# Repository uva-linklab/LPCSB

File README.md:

# LPCSB
LPCSB = Low Power Color Sensing Board

The LPCSB is designed to measure the ambient light in the surrounding area by means of a TCS34725 Color Sensor.  The sensor uses four analog-to-digital converters (ADCs) to read four photodiodes (one photodiode per ADC).  The photodiodes are red-filtered, green-filtered, blue-filtered, and clear (no filter).  The photodiodes are also covered with an IR-blocking filter.  The code in the "software" folder of this repository is responsible for initializing all of the hardware on the LPCSB, configuring the settings of the color sensor (integration time, gain, enabling the internal oscillator, enabling the ADCs, and setting a hardware interrupt in the sensor), reading and saving the values taken by the four ADCs mentioned previously, and then calculating the the temperature of each color (how much of each is in the sample taken), as well as the lux (intensity per square meter) of said sample.  The measured color temperatures along with the calculated values are broadcast through the BLE radio built into the nrf51822 processor used in this board several times, with new measurements being taken every five seconds.  

There is also a data-processing algorithm that is meant to operate on a desktop computer, using  a Bluetooth receiver - see thesis for the specific one - to capture the transmitted data from the LPCSB and save it to an Excel spreadsheet.  Depending on the version of the algorithm being used, it can also classify the type of light measured by the LPCSB before saving the data to Excel.  When running tests with the LPCSB, make sure that the algorithm is running BEFORE activating the LPCSB to avoid errors with the algorithm in its current state.

SIDE NOTE:  Make sure that the external crystal oscillator meets the BLE chip requirements for the external clock frequency described in the nrf51822 datasheet. In this case, the required frequency for the external clock is 16 MHz.  For some reason, the clock chips that were being used early on were 26 MHz clocks instead of 16 MHz, which WILL cause errors with whichever sections of the processor happen to rely on the external signal (in this case, the BLE Radio parts).

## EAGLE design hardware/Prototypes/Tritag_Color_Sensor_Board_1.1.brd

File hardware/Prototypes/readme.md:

# Version 1:

The files in this folder hold prototype schematics for potential additions for the LPCSB (layout and schematic files).

Label the prototype files as follows: LPCSB_Color_[insert new sensor name here]_[board or schematic]

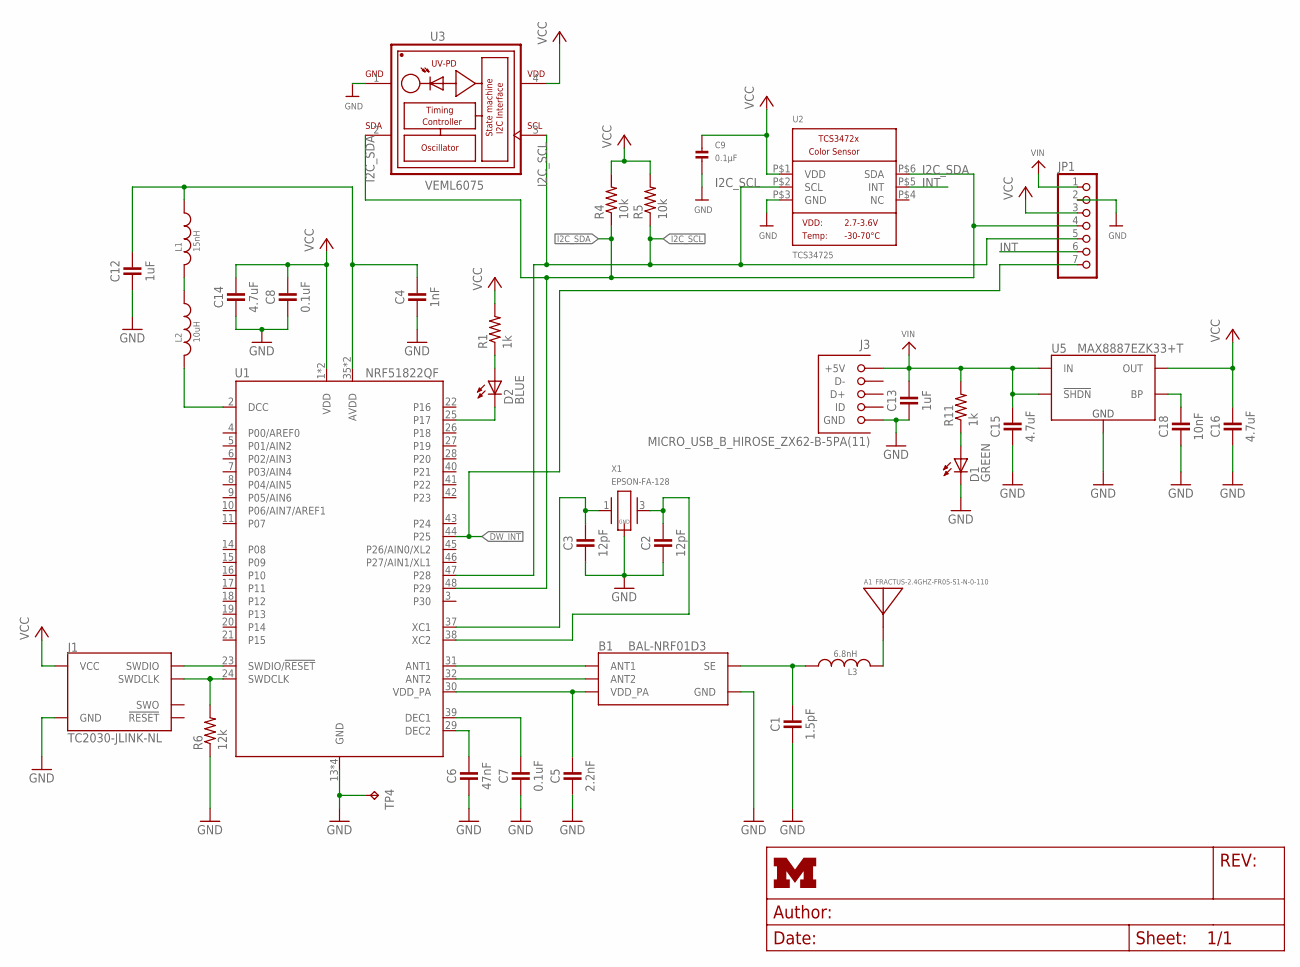
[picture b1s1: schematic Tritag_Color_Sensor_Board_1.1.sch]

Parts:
A1: FRACTUS-2.4GHZ-FR05-S1-N-0-110; FRACTUS-ANTENNA-FR05-S1-N-0-110
B1: BAL-NRF01D3
C1: 1.5pF; 0402_CAP
C2, C3: 12pF; 0402_CAP
C4: 1nF; 0402_CAP
C5: 2.2nF; 0402_CAP
C6: 47nF; 0402_CAP
C7, C8: 0.1uF; 0402_CAP
C9: 0.1µF; _0805
C12, C13: 1uF; 0402_CAP
C14, C15, C16: 4.7uF; 0402_CAP
C18: 10nF; 0402_CAP
D1: GREEN; LED-0603
D2: BLUE; LED-0603
J1: TC2030-JLINK-NL; TC2030-IDC-NL
J3: MICRO_USB_B_HIROSE_ZX62-B-5PA(11); USB_MICRO_B-HIROSE-ZX62-B-5PA(11)
JP1: HEADER-1X770MIL; 1X07_ROUND_70
L1: 15nH; 0402_CAP
L2: 10uH; 0603_CAP
L3: 6.8nH; 0402_CAP
R1, R11: 1k; 0402_RES
R4, R5: 10k; 0402_RES
R6: 12k; 0402_RES
TP4: TPTP06SQ; TP06SQ
U1: NRF51822QF; QFN-48-6MM
U2: TCS34725; TCS3472_FN6
U3: VEML6075; VISHAY_VEML6075_1.25X2X1
U5: MAX8887EZK33+T; SOT-23-5
X1: EPSON-FA-128; FA-128

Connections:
!CHRG: D1.A, R11.1
!CHRG1: D2.A, R1.1
ANTENNA: A1.ANT, L3.2
AVDD: C4.1, C12.1, L1.1, U1.35 (AVDD), U1.36 (AVDD)
DCC: L2.2, U1.2 (DCC)
DW_INT: JP1.7, U1.44 (P25)
GND: B1.GND, C1.2, C2.2, C3.2, C4.2, C5.2, C6.2, C7.2, C8.2, C9.2, C12.2, C13.2, C14.2, C15.2, C16.2, C18.2, D1.C, J1.5 (GND), J3.5 (GND), JP1.2, R6.1, TP4.TP, U1.13 (GND), U1.33 (GND), U1.34 (GND), U1.GND, U2.P$3 (GND), U3.1 (GND), U5.2 (GND), X1.2 (GND), X1.4 (GND)
I2C_SCL: JP1.5, R5.1, U1.47 (P28), U2.P$2 (SCL), U3.3 (SCL)
I2C_SDA: JP1.4, R4.1, U1.48 (P29), U2.P$6 (SDA), U3.2 (SDA)
INT: JP1.6, U2.P$5 (INT)
unnamed: B1.SE, C1.1, L3.1
unnamed: D2.C, U1.25 (P17)
unnamed: C3.1, U1.37 (XC1), X1.1
unnamed: C2.1, U1.38 (XC2), X1.3 (2)
unnamed: C18.1, U5.4 (BP)
unnamed: C6.1, U1.29 (DEC2)
unnamed: C7.1, U1.39 (DEC1)
unnamed: B1.ANT1, U1.31 (ANT1)
unnamed: B1.ANT2, U1.32 (ANT2)
unnamed: B1.VCC (VDD_PA), C5.1, U1.30 (VDD_PA)
unnamed: L1.2, L2.1
SWDCLK: J1.4 (SWDCLK), R6.2, U1.24 (SWDCLK)
SWDIO/!RESET: J1.2 (SWDIO), U1.23 (SWDIO/!RESET)
VCC: C8.1, C9.1, C14.1, C16.1, J1.1 (VCC), JP1.3, R1.2, R4.2, R5.2, U1.1 (VDD), U1.12 (VDD), U2.P$1 (VDD), U3.4 (VDD), U5.5 (OUT)
VIN: C13.1, C15.1, J3.1 (+5V), JP1.1, R11.2, U5.1 (IN), U5.3 (!SHDN)

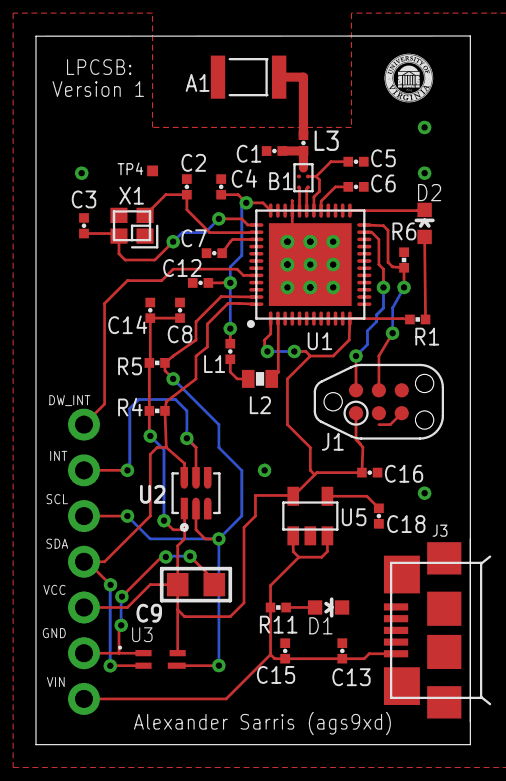
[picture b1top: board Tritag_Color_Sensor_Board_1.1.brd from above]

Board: 2 copper layers, 24.1 x 39.4 mm, 36 parts (0 on the bottom side), 25 nets.

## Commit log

2018-11-24 Need to add final methods
    All necessary methods for configuring the sensor and reading color values are up and running. Need to uncomment and test the methods for calculating color temperature and lux. Also need to write and 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
2018-11-24 Updated with more details
2019-02-28 Update Files
    The board is now able to read the sensor once and broadcast the data
2019-02-28 Added ReadMe
2019-03-08 Adding Full Code
    Board is set to broadcast data once over every five seconds with "simple" and "eddystone" Bluetooth libraries. Am currently working on the HTML file for the web page to display the data sent through 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
2019-03-14 Create index.js for Eddystone testing
2019-03-14 Converted to html
    Javascript version of the file was in error, should be HTML
2019-03-14 Added other summon files
2019-03-14 Adding files
2019-03-15 Testing something
2019-03-15 Test
2019-03-15 Replacing files
2019-03-15 Update index.js to work with LPCSB instead of herald
2019-07-08 Update main.c
    Added sequence number between sensorID and color data
2019-09-09 Adding PCB Files
2019-09-09 Add PCB gerber files
2019-09-09 Update board files
2019-09-30 New prototype with VEML6075 UV sensor
2019-12-17 Updates
    Added an app that will ID the type of light on the PCB and updated the original app
2020-05-20 Algorithm
    Added data processing and light-ID'ing algorithms
2020-05-20 Changed folder name
    Better idea of what's inside from folder name

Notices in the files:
parts and their libraries:
SparkFun-LED: Licensing: CC v3.0 Share-Alike You are welcome to use this library for commercial purposes.
microbuilder: This work is placed in the public domain, and may be freely used for commercial and non-commercial work with the following conditions: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
